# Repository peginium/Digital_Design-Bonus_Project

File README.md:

# 4x4 Matrix Keypad

## 📖 Genel Bakış
Bu repo, **ESP32** ve **FPGA** üzerinde gerçekleştirilmiş bir **4x4 Matris Keypad** tasarımını ve uygulamasını içerir. Ayrıca **KiCad** ile tasarlanmış özel bir PCB tasarımını da içermektedir.

## 📂 Klasör Yapısı

```text
├── 📁 keypad_fpga/         # Basys3 için Verilog tasarımı
│   ├── keypad.v        # Verilog kaynak kodu
│   └── Basys-3-Master.xdc     # Basys3 için pin planlaması 
├── 📁 keypad_mcu/       # ESP32 için C kodları
│   ├── keypad.ino
├── 📁 kicad_design/         # PCB tasarım Dosyaları
│   ├── keypad.kicad_sch  # Şematik Dosyası
│   └── keypad.kicad_pcb  # PCB layout
└── README.md

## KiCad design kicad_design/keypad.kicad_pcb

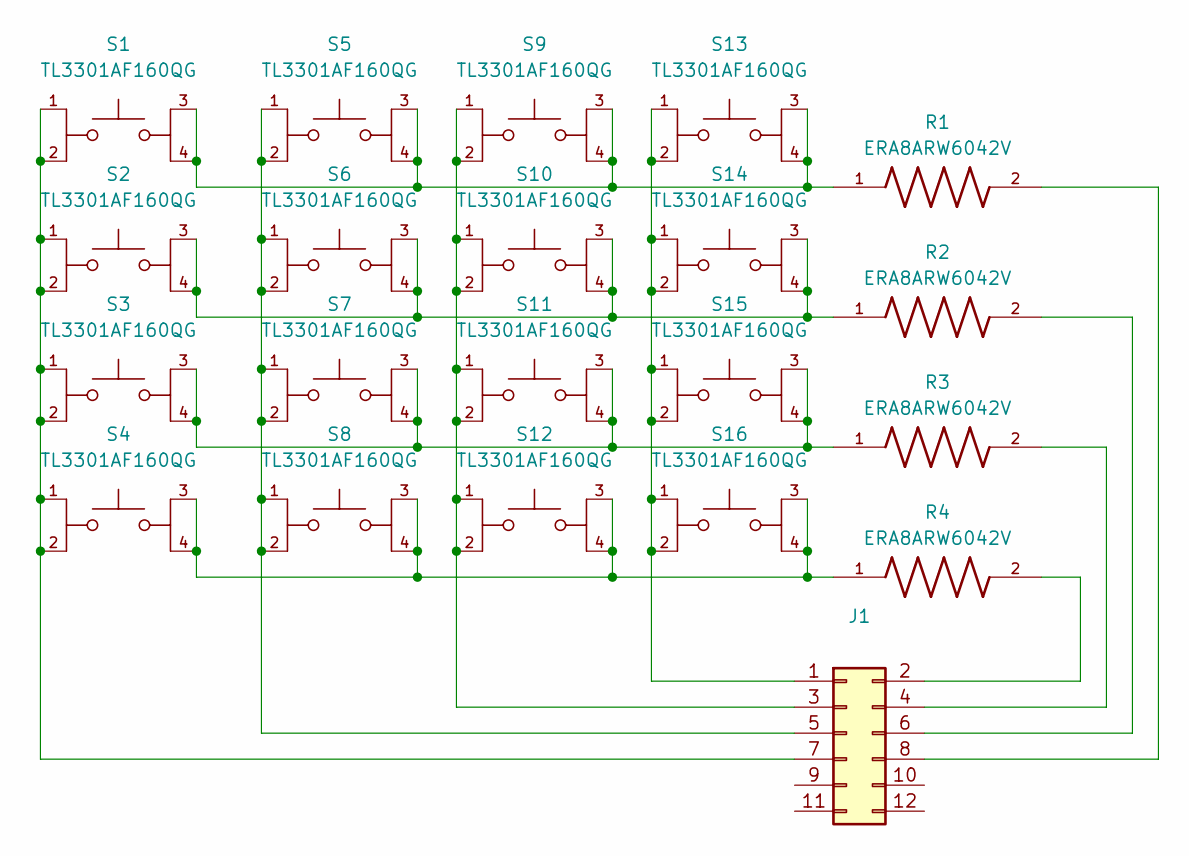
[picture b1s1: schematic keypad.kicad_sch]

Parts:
J1: Conn_02x06_Odd_Even; PinHeader_2x06_P2.54mm_Vertical
R1, R2, R3, R4: ERA8ARW6042V; RES_ERA8ARW6042V; PARTREV 3/1/2020
S1, S2, S3, S4, S5, S6, S7, S8, S9, S10, S11, S12, S13, S14, S15, S16: TL3301AF160QG; TL1100F160Q; PARTREV E

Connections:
unnamed: J1.1, S13.1, S13.2, S14.1, S14.2, S15.1, S15.2, S16.1, S16.2
unnamed: J1.2, R4.2
unnamed: J1.3, S9.1, S9.2, S10.1, S10.2, S11.1, S11.2, S12.1, S12.2
unnamed: J1.4, R3.2
unnamed: J1.5, S5.1, S5.2, S6.1, S6.2, S7.1, S7.2, S8.1, S8.2
unnamed: J1.6, R2.2
unnamed: J1.7, S1.1, S1.2, S2.1, S2.2, S3.1, S3.2, S4.1, S4.2
unnamed: J1.8, R1.2
unnamed: R1.1, S1.3, S1.4, S5.3, S5.4, S9.3, S9.4, S13.3, S13.4
unnamed: R2.1, S2.3, S2.4, S6.3, S6.4, S10.3, S10.4, S14.3, S14.4
unnamed: R3.1, S3.3, S3.4, S7.3, S7.4, S11.3, S11.4, S15.3, S15.4
unnamed: R4.1, S4.3, S4.4, S8.3, S8.4, S12.3, S12.4, S16.3, S16.4

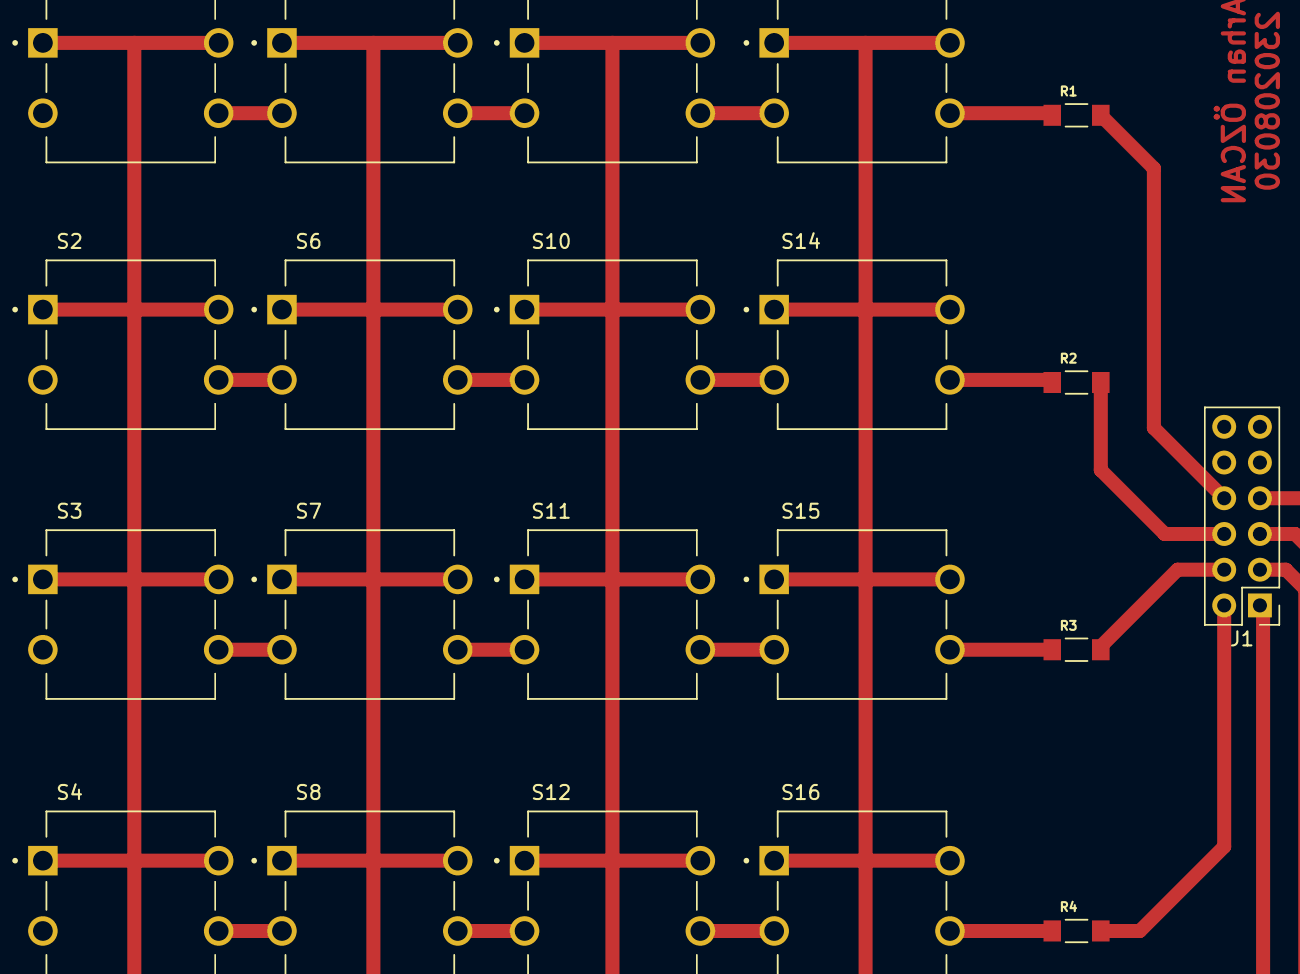
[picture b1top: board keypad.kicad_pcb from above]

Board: 2 copper layers, 21 parts (0 on the bottom side), 12 nets.

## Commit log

2026-01-08 Create kicad_design
2026-01-08 Dosyalar Eklendi
